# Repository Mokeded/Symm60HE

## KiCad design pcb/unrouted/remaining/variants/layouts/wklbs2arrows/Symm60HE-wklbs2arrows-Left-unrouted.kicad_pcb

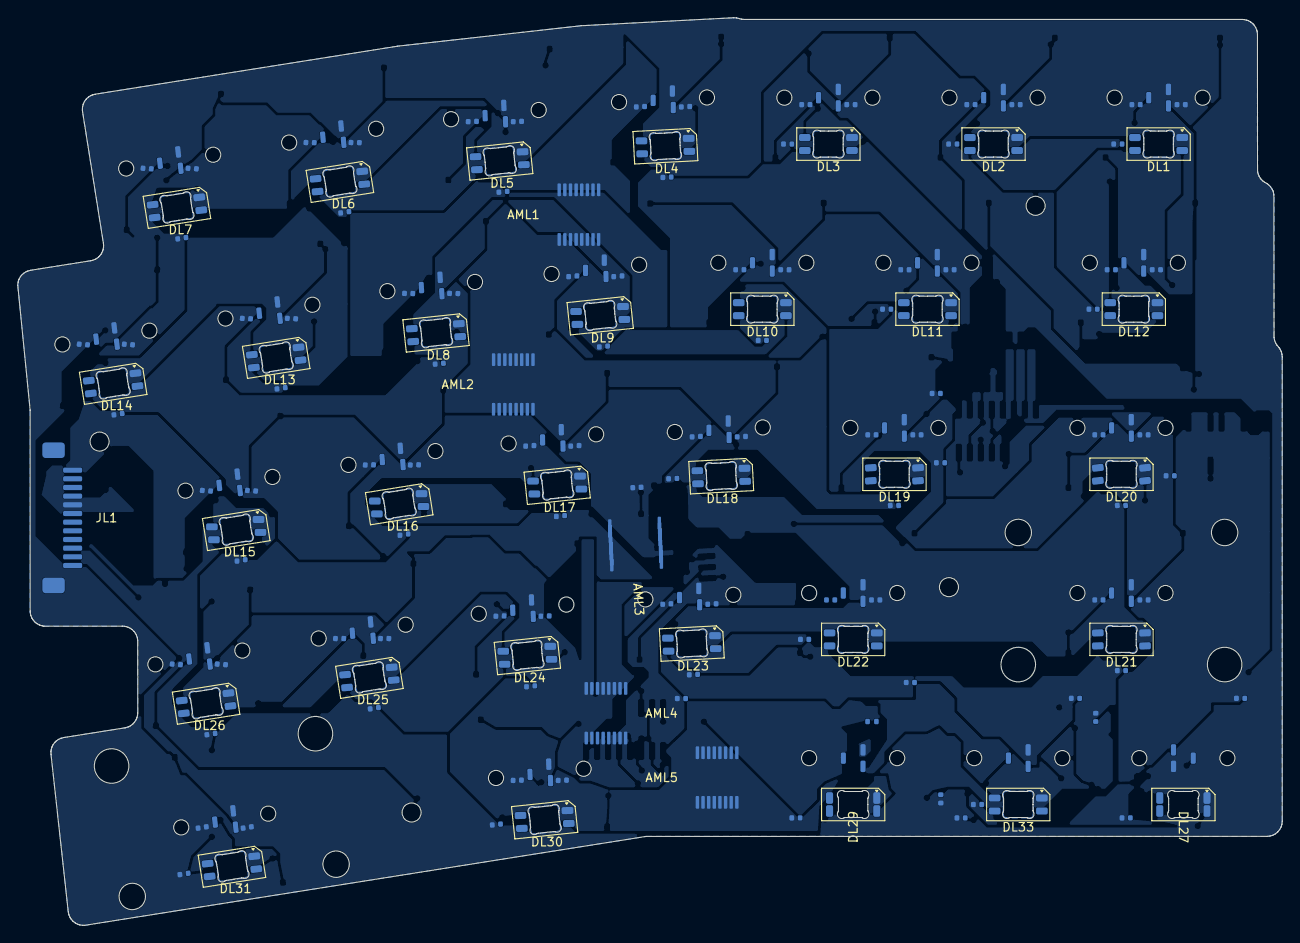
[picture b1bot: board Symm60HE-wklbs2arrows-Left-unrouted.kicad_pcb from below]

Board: 2 copper layers, 145.9 x 104.7 mm, 173 parts (167 on the bottom side), 73 nets, no tracks yet.

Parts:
AML1, AML2, AML3, AML4, AML5: SN74LV4051A; AM1_TSSOP-16_4.4x5mm_P0.65mm
CL1A, CL2A, CL3A, CL4A, CL5A, CL6A, CL7A, CL8A, CL9A, CL10A, CL11A, CL12A, CL13A, CL14A, CL15A, CL16A, CL17A, CL18A, CL19A, CL20A, CL21A, CL22A, CL23A, CL24A, CL25A, CL26A, CL27A, CL29A, CL31A, CL32A, CL33A: 100n; C1_C_0402_1005Metric
CL1B, CL2B, CL3B, CL4B, CL5B, CL6B, CL7B, CL8B, CL9B, CL10B, CL11B, CL12B, CL13B, CL14B, CL15B, CL16B, CL17B, CL18B, CL19B, CL20B, CL21B, CL22B, CL23B, CL24B, CL25B, CL26B, CL27B, CL29B, CL31B, CL32B, CL33B: 4.7n; C1_C_0402_1005Metric
CML1, CML2, CML3, CML4, CML5: 100n; C1_C_0402_1005Metric
CRGBL1, CRGBL2, CRGBL3, CRGBL4, CRGBL5, CRGBL6, CRGBL7, CRGBL8, CRGBL9, CRGBL10, CRGBL11, CRGBL12, CRGBL13, CRGBL14, CRGBL15, CRGBL16, CRGBL17, CRGBL18, CRGBL19, CRGBL20, CRGBL21, CRGBL22, CRGBL23, CRGBL24, CRGBL25, CRGBL26, CRGBL27, CRGBL29, CRGBL30, CRGBL31, CRGBL33: 100n; C1_C_0402_1005Metric
DL1, DL2, DL3, DL4, DL5, DL6, DL7, DL8, DL9, DL10, DL11, DL12, DL13, DL14, DL15, DL16, DL17, DL18, DL19, DL20, DL21, DL22, DL23, DL24, DL25, DL26, DL27, DL29, DL30, DL31, DL33: SK6812MINI-E; SK6812MINI-E_ReverseMount
HEL1, HEL2, HEL3, HEL4, HEL5, HEL6, HEL7, HEL9, HEL10, HEL11, HEL12, HEL13, HEL14, HEL16, HEL17, HEL18, HEL19, HEL20, HEL22, HEL23, HEL24, HEL25, HEL26, HEL27, HEL29, HEL31: MT9102ET; HE_KEY_1.00u
HEL8, HEL32: MT9102ET; HE_KEY_1.50u
HEL15: MT9102ET; HE_KEY_1.75u
HEL21, HEL33: MT9102ET; HE_KEY_2.25u
JL1: FFC_12P; FFC_12P_1.00mm_TopContact
MHL1, MHL2, MHL3, MHL4: M2_NPTH; MountingHole_2.2mm_M2_NPTH
RBPL29: 0R_DNP; R3_R_0402_1005Metric
SL1, SL2: STAB_MX; STABILIZER_MX_2U

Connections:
+3V3A: AML1.16, AML2.16, AML3.16, AML4.16, AML5.16, CL1A.1, CL2A.1, CL3A.1, CL4A.1, CL5A.1, CL6A.1, CL7A.1, CL8A.1, CL9A.1, CL10A.1, CL11A.1, CL12A.1, CL13A.1, CL14A.1, CL15A.1, CL16A.1, CL17A.1, CL18A.1, CL19A.1, CL20A.1, CL21A.1, CL22A.1, CL23A.1, CL24A.1, CL25A.1, CL26A.1, CL27A.1, CL29A.1, CL31A.1, CL32A.1, CL33A.1, CML1.1, CML2.1, CML3.1, CML4.1, CML5.1, HEL1.1, HEL2.1, HEL3.1, HEL4.1, HEL5.1, HEL6.1, HEL7.1, HEL8.1, HEL9.1, HEL10.1, HEL11.1, HEL12.1, HEL13.1, HEL14.1, HEL15.1, HEL16.1, HEL17.1, HEL18.1, HEL19.1, HEL20.1, HEL21.1, HEL22.1, HEL23.1, HEL24.1, HEL25.1, HEL26.1, HEL27.1, HEL29.1, HEL31.1, HEL32.1, HEL33.1, JL1.12
ADC_L1: AML1.3, JL1.6
ADC_L2: AML2.3, JL1.4
ADC_L3: AML3.3, JL1.2
ADC_L4: AML4.3, JL1.1
ADC_L5: AML5.3, JL1.11
GND: AML1.6, AML1.7, AML1.8, AML2.6, AML2.7, AML2.8, AML3.6, AML3.7, AML3.8, AML4.4, AML4.6, AML4.7, AML4.8, AML5.1, AML5.2, AML5.4, AML5.5, AML5.6, AML5.7, AML5.8, AML5.12, AML5.15, CL1A.2, CL1B.2, CL2A.2, CL2B.2, CL3A.2, CL3B.2, CL4A.2, CL4B.2, CL5A.2, CL5B.2, CL6A.2, CL6B.2, CL7A.2, CL7B.2, CL8A.2, CL8B.2, CL9A.2, CL9B.2, CL10A.2, CL10B.2, CL11A.2, CL11B.2, CL12A.2, CL12B.2, CL13A.2, CL13B.2, CL14A.2, CL14B.2, CL15A.2, CL15B.2, CL16A.2, CL16B.2, CL17A.2, CL17B.2, CL18A.2, CL18B.2, CL19A.2, CL19B.2, CL20A.2, CL20B.2, CL21A.2, CL21B.2, CL22A.2, CL22B.2, CL23A.2, CL23B.2, CL24A.2, CL24B.2, CL25A.2, CL25B.2, CL26A.2, CL26B.2, CL27A.2, CL27B.2, CL29A.2, CL29B.2, CL31A.2, CL31B.2, CL32A.2, CL32B.2, CL33A.2, CL33B.2, CML1.2, CML2.2, CML3.2, CML4.2, CML5.2, CRGBL1.2, CRGBL2.2, CRGBL3.2, CRGBL4.2, CRGBL5.2, CRGBL6.2, CRGBL7.2, CRGBL8.2, CRGBL9.2, CRGBL10.2, CRGBL11.2, CRGBL12.2, CRGBL13.2, CRGBL14.2, CRGBL15.2, CRGBL16.2, CRGBL17.2, CRGBL18.2, CRGBL19.2, CRGBL20.2, CRGBL21.2, CRGBL22.2, CRGBL23.2, CRGBL24.2, CRGBL25.2, CRGBL26.2, CRGBL27.2, CRGBL29.2, CRGBL30.2, CRGBL31.2, CRGBL33.2, DL1.1, DL2.1, DL3.1, DL4.1, DL5.1, DL6.1, DL7.1, DL8.1, DL9.1, DL10.1, DL11.1, DL12.1, DL13.1, DL14.1, DL15.1, DL16.1, DL17.1, DL18.1, DL19.1, DL20.1, DL21.1, DL22.1, DL23.1, DL24.1, DL25.1, DL26.1, DL27.1, DL29.1, DL30.1, DL31.1, DL33.1, HEL1.2, HEL2.2, HEL3.2, HEL4.2, HEL5.2, HEL6.2, HEL7.2, HEL8.2, HEL9.2, HEL10.2, HEL11.2, HEL12.2, HEL13.2, HEL14.2, HEL15.2, HEL16.2, HEL17.2, HEL18.2, HEL19.2, HEL20.2, HEL21.2, HEL22.2, HEL23.2, HEL24.2, HEL25.2, HEL26.2, HEL27.2, HEL29.2, HEL31.2, HEL32.2, HEL33.2, JL1.5
HE_L01: AML1.13, CL1B.1, HEL1.3
HE_L02: AML1.14, CL2B.1, HEL2.3
HE_L03: AML1.15, CL3B.1, HEL3.3
HE_L04: AML1.12, CL4B.1, HEL4.3
HE_L05: AML1.1, CL5B.1, HEL5.3
HE_L06: AML1.5, CL6B.1, HEL6.3
HE_L07: AML1.2, CL7B.1, HEL7.3
HE_L08: AML1.4, CL8B.1, HEL8.3
HE_L09: AML2.13, CL9B.1, HEL9.3
HE_L10: AML2.14, CL10B.1, HEL10.3
HE_L11: AML2.15, CL11B.1, HEL11.3
HE_L12: AML2.12, CL12B.1, HEL12.3
HE_L13: AML2.1, CL13B.1, HEL13.3
HE_L14: AML2.5, CL14B.1, HEL14.3
HE_L15: AML2.2, CL15B.1, HEL15.3
HE_L16: AML2.4, CL16B.1, HEL16.3
HE_L17: AML3.13, CL17B.1, HEL17.3
HE_L18: AML3.14, CL18B.1, HEL18.3
HE_L19: AML3.15, CL19B.1, HEL19.3
HE_L20: AML3.12, CL20B.1, HEL20.3
HE_L21: AML3.1, CL21B.1, HEL21.3
HE_L22: AML3.5, CL22B.1, HEL22.3
HE_L23: AML3.2, CL23B.1, HEL23.3
HE_L24: AML3.4, CL24B.1, HEL24.3
HE_L25: AML4.13, CL25B.1, HEL25.3
HE_L26: AML4.14, CL26B.1, HEL26.3
HE_L27: AML4.15, CL27B.1, HEL27.3
HE_L28: AML4.12, CL29B.1, HEL29.3
HE_L29: AML4.1, CL31B.1, HEL31.3
HE_L30: AML4.5, CL32B.1, HEL32.3
HE_L31: AML4.2, CL33B.1, HEL33.3
MUX_A0: AML1.11, AML2.11, AML3.11, AML4.11, AML5.11, JL1.10
MUX_A1: AML1.10, AML2.10, AML3.10, AML4.10, AML5.10, JL1.9
MUX_A2: AML1.9, AML2.9, AML3.9, AML4.9, AML5.9, JL1.8
RGB_L: DL1.2, JL1.3
RGB_L_01: DL1.4, DL2.2
RGB_L_02: DL2.4, DL3.2
RGB_L_03: DL3.4, DL4.2
RGB_L_04: DL4.4, DL5.2
RGB_L_05: DL5.4, DL6.2
RGB_L_06: DL6.4, DL7.2
RGB_L_07: DL7.4, DL8.2
RGB_L_08: DL8.4, DL9.2
RGB_L_09: DL9.4, DL10.2
RGB_L_10: DL10.4, DL11.2
RGB_L_11: DL11.4, DL12.2
RGB_L_12: DL12.4, DL13.2
RGB_L_13: DL13.4, DL14.2
RGB_L_14: DL14.4, DL15.2
RGB_L_15: DL15.4, DL16.2
RGB_L_16: DL16.4, DL17.2
RGB_L_17: DL17.4, DL18.2
RGB_L_18: DL18.4, DL19.2
RGB_L_19: DL19.4, DL20.2
RGB_L_20: DL20.4, DL21.2
RGB_L_21: DL21.4, DL22.2
RGB_L_22: DL22.4, DL23.2
RGB_L_23: DL23.4, DL24.2
RGB_L_24: DL24.4, DL25.2
RGB_L_25: DL25.4, DL26.2
RGB_L_26: DL26.4, DL27.2
RGB_L_27: DL27.4, DL33.2
RGB_L_28: DL29.2, DL33.4, RBPL29.1
RGB_L_29: DL29.4, DL30.2, RBPL29.2
RGB_L_30: DL30.4, DL31.2
VBUS: CRGBL1.1, CRGBL2.1, CRGBL3.1, CRGBL4.1, CRGBL5.1, CRGBL6.1, CRGBL7.1, CRGBL8.1, CRGBL9.1, CRGBL10.1, CRGBL11.1, CRGBL12.1, CRGBL13.1, CRGBL14.1, CRGBL15.1, CRGBL16.1, CRGBL17.1, CRGBL18.1, CRGBL19.1, CRGBL20.1, CRGBL21.1, CRGBL22.1, CRGBL23.1, CRGBL24.1, CRGBL25.1, CRGBL26.1, CRGBL27.1, CRGBL29.1, CRGBL30.1, CRGBL31.1, CRGBL33.1, DL1.3, DL2.3, DL3.3, DL4.3, DL5.3, DL6.3, DL7.3, DL8.3, DL9.3, DL10.3, DL11.3, DL12.3, DL13.3, DL14.3, DL15.3, DL16.3, DL17.3, DL18.3, DL19.3, DL20.3, DL21.3, DL22.3, DL23.3, DL24.3, DL25.3, DL26.3, DL27.3, DL29.3, DL30.3, DL31.3, DL33.3, JL1.7

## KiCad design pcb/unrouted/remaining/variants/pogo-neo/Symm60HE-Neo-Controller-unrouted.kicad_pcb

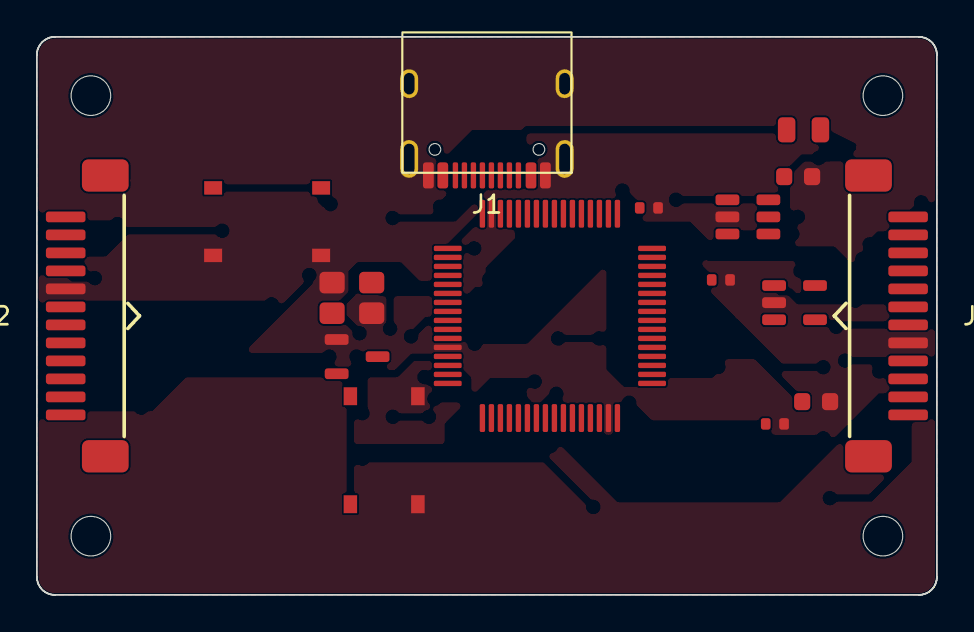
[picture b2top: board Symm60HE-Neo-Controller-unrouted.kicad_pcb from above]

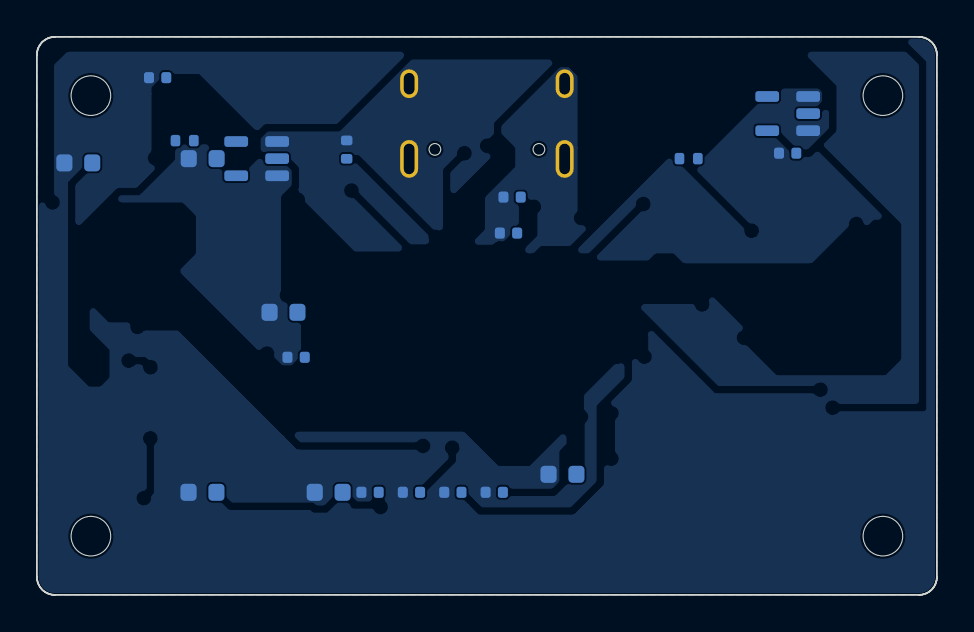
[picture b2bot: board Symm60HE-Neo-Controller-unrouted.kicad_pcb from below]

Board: 2 copper layers, 50.0 x 31.0 mm, 40 parts (20 on the bottom side), 33 nets, no tracks yet.

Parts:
C1, C8: 10u; C148_C_0603_1608Metric
C2, C10: 1u; C148_C_0603_1608Metric
C3, C4: 30p; C1_C_0402_1005Metric
C5, C6, C7, C9, C11, C16, C17: 100n; C1_C_0402_1005Metric
C12, C13, C14, C15: 2.2u; C148_C_0603_1608Metric
F1: 0.5A; F1_Fuse_0805_2012Metric
J1: TYPE-C-31-M-12; USB_C_Receptacle_HRO_TYPE-C-31-M-12
J2, J3: FFC_12P; FFC_12P_1.00mm_TopContact
MHD1, MHD2, MHD3, MHD4: M2_NPTH; MountingHole_2.2mm_M2_NPTH
R1, R4: 12k; R3_R_0402_1005Metric
R2, R3: 5.1k; R3_R_0402_1005Metric
R5, R6: 470R; R3_R_0402_1005Metric
SW1, SW2: TS-1187A; SW1_SW_Push_1P1T_XKB_TS-1187A
U1: AT32F405RCT7; U4_LQFP-64_10x10mm_P0.5mm
U2: USBLC6-2SC6; U1_SOT-23-6
U3: TLV75733PDBV; U2_SOT-23-5
U4: XC6206P332MR; U3_SOT-23-3
U5, U6: SN74AHCT1G125; U2_SOT-23-5
Y1: 12MHz; Y1_Crystal_SMD_3225-4Pin_3.2x2.5mm

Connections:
+3V3A: C9.1, C10.1, C15.1, J2.1, J3.1, U1.13, U4.2
+3V3D: C2.1, C5.1, C6.1, C7.1, C8.1, C13.1, C14.1, U1.1, U1.36, U1.64, U3.5, U4.3
ADC_L1: J2.7, U1.17
ADC_L2: J2.9, U1.20
ADC_L3: J2.11, U1.21
ADC_L4: J2.12, U1.22
ADC_L5: J2.2, U1.16
ADC_R1: J3.7, U1.23
ADC_R2: J3.9, U1.24
ADC_R3: J3.11, U1.25
ADC_R4: J3.12, U1.26
ADC_R5: J3.2, U1.15
BOOT0: R4.1, SW1.1, U1.60
CC1: J1.A5, R2.1
CC2: J1.B5, R3.1
GND: C1.2, C2.2, C3.2, C4.2, C5.2, C6.2, C7.2, C8.2, C9.2, C10.2, C11.2, C12.2, C13.2, C14.2, C15.2, C16.2, C17.2, J1.A1, J1.A12, J1.B1, J1.B12, J1.SH, J2.8, J3.8, R1.2, R2.2, R3.2, R4.2, SW1.2, SW2.2, U1.12, U1.31, U1.63, U2.2, U3.2, U4.1, U5.1, U5.3, U6.1, U6.3, Y1.2, Y1.4
MUX_A0: J2.3, J3.3, U1.9
MUX_A1: J2.4, J3.4, U1.10
MUX_A2: J2.5, J3.5, U1.11
NRST: C11.1, SW2.1, U1.7
RGB_L: J2.10, R5.2
RGB_L_BUF: R5.1, U5.4
RGB_L_MCU: U1.8, U5.2
RGB_R: J3.10, R6.2
RGB_R_BUF: R6.1, U6.4
RGB_R_MCU: U1.41, U6.2
USB_DM: J1.A7, J1.B7, U1.34, U2.3, U2.4
USB_DP: J1.A6, J1.B6, U1.35, U2.1, U2.6
USB_R: R1.1, U1.33
VBUS: C1.1, C12.1, C16.1, C17.1, F1.2, J2.6, J3.6, U2.5, U3.1, U5.5, U6.5
VBUS_IN: F1.1, J1.A4, J1.A9, J1.B4, J1.B9
XTAL_IN: C3.1, U1.5, Y1.1
XTAL_OUT: C4.1, U1.6, Y1.3

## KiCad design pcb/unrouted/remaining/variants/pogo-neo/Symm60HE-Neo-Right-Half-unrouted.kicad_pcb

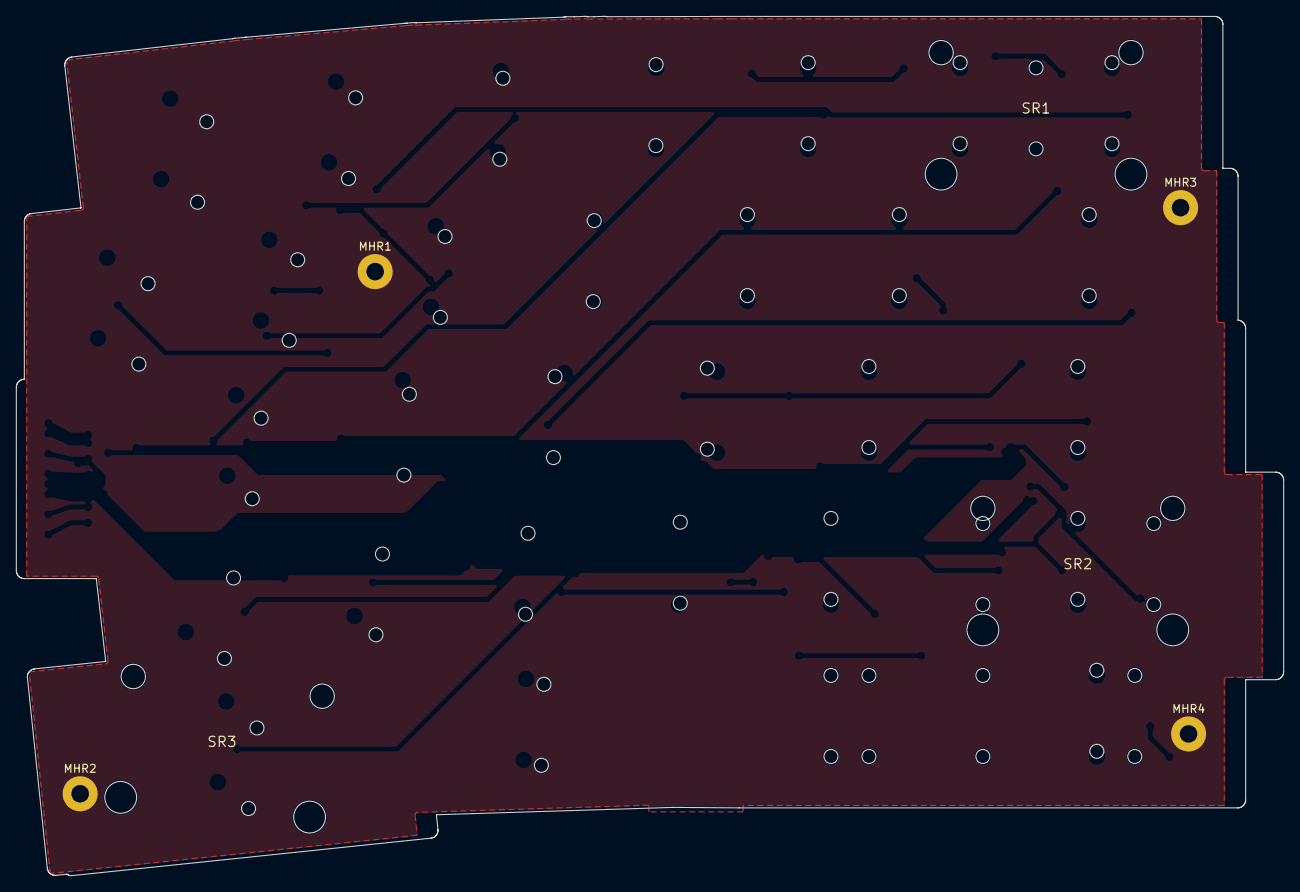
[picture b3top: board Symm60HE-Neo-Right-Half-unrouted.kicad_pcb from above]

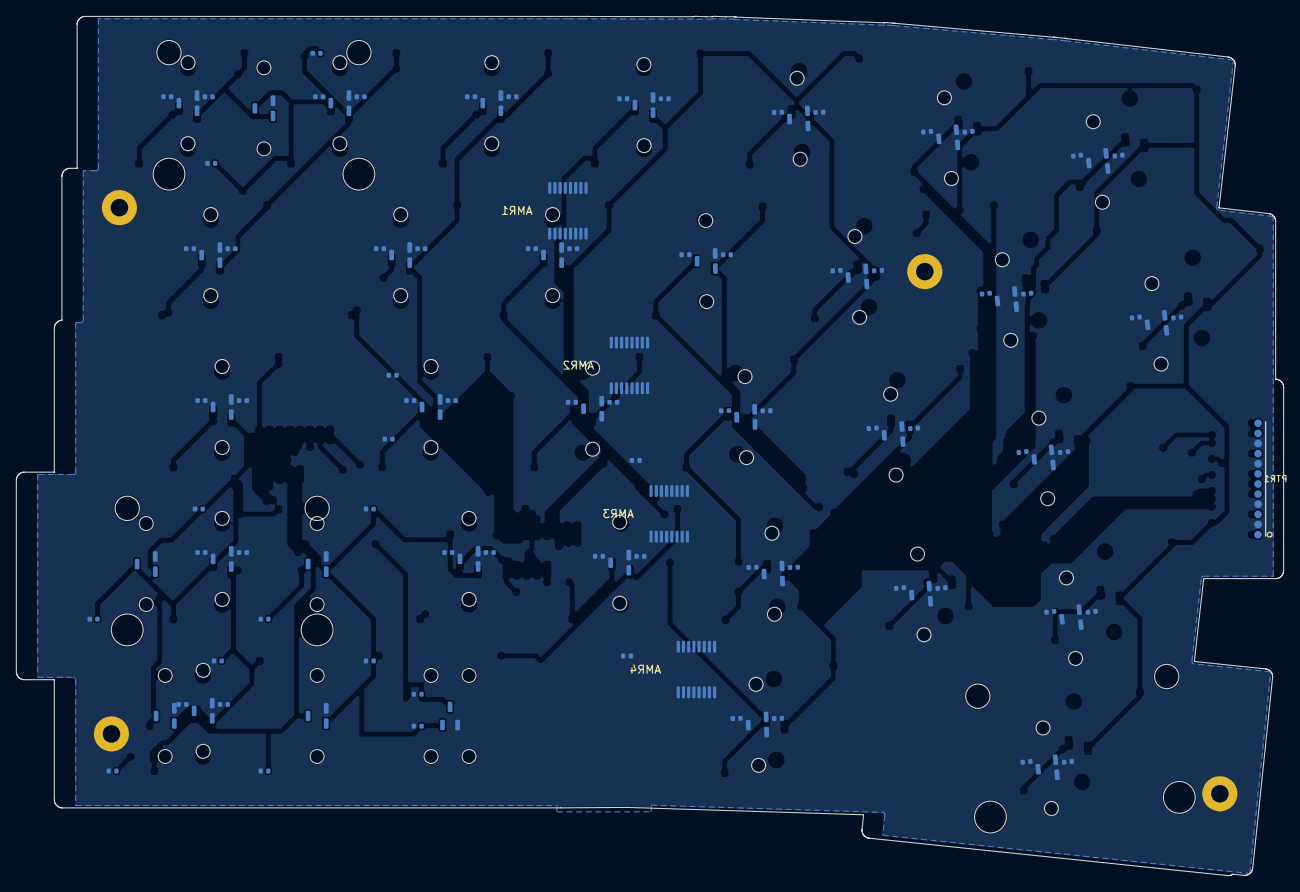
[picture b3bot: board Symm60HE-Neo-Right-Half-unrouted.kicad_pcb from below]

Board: 2 copper layers, 158.9 x 107.8 mm, 123 parts (116 on the bottom side), 41 nets, no tracks yet.

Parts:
AMR1, AMR2, AMR3, AMR4: SN74LV4051A; AM1_TSSOP-16_4.4x5mm_P0.65mm
CMR1, CMR2, CMR3, CMR4: 100n; C1_C_0402_1005Metric
CR1A, CR2A, CR3A, CR4A, CR5A, CR6A, CR7A, CR8A, CR9A, CR10A, CR11A, CR12A, CR13A, CR14A, CR15A, CR16A, CR17A, CR18A, CR19A, CR20A, CR21A, CR22A, CR23A, CR24A, CR25A, CR26A, CR27A, CR28A, CR29A, CR30A, CR32A, CR33A, CR34A, CR35A, CR36A: 100n; C1_C_0402_1005Metric
CR1B, CR2B, CR3B, CR4B, CR5B, CR6B, CR7B, CR8B, CR9B, CR10B, CR11B, CR12B, CR13B, CR14B, CR15B, CR16B, CR17B, CR18B, CR19B, CR20B, CR21B, CR22B, CR23B, CR24B, CR25B, CR26B, CR27B, CR28B, CR29B, CR30B, CR32B, CR33B, CR34B, CR35B, CR36B: 4.7n; C1_C_0402_1005Metric
HER1, HER2, HER3, HER5, HER6, HER7, HER8, HER9, HER10, HER12, HER13, HER14, HER15, HER16, HER17, HER19, HER20, HER21, HER22, HER23, HER24, HER27, HER28, HER29, HER32, HER34: MT9102ET; HE_KEY_1.00u
HER4: MT9102ET; HE_KEY_2.00u
HER11, HER33, HER35: MT9102ET; HE_KEY_1.50u
HER18: MT9102ET; HE_KEY_1.75u
HER25, HER36: MT9102ET; HE_KEY_2.25u
HER26: MT9102ET; HE_KEY_1.25u
HER30: MT9102ET; HE_SHARED_MIDPOINT
KMR30A, KMR30N: MX_MECHANICAL_ONLY; HE_KEY_MECHANICAL_ONLY
MHR1, MHR2, MHR3, MHR4: M2; MountingHole_2.2mm_M2_Pad
PTR1: 856-10-012-30-051000; MillMax_856-10-012-30-051000
SR1, SR2, SR3: STAB_MX; STABILIZER_MX_2U

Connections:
+3V3A: AMR1.16, AMR2.16, AMR3.16, AMR4.16, CMR1.1, CMR2.1, CMR3.1, CMR4.1, CR1A.1, CR2A.1, CR3A.1, CR4A.1, CR5A.1, CR6A.1, CR7A.1, CR8A.1, CR9A.1, CR10A.1, CR11A.1, CR12A.1, CR13A.1, CR14A.1, CR15A.1, CR16A.1, CR17A.1, CR18A.1, CR19A.1, CR20A.1, CR21A.1, CR22A.1, CR23A.1, CR24A.1, CR25A.1, CR26A.1, CR27A.1, CR28A.1, CR29A.1, CR30A.1, CR32A.1, CR33A.1, CR34A.1, CR35A.1, CR36A.1, HER1.1, HER2.1, HER3.1, HER4.1, HER5.1, HER6.1, HER7.1, HER8.1, HER9.1, HER10.1, HER11.1, HER12.1, HER13.1, HER14.1, HER15.1, HER16.1, HER17.1, HER18.1, HER19.1, HER20.1, HER21.1, HER22.1, HER23.1, HER24.1, HER25.1, HER26.1, HER27.1, HER28.1, HER29.1, HER30.1, HER32.1, HER33.1, HER34.1, HER35.1, HER36.1, PTR1.1
ADC_R1: AMR1.3, PTR1.7
ADC_R2: AMR2.3, PTR1.9
ADC_R3: AMR3.3, PTR1.11
ADC_R4: AMR4.3, PTR1.12
GND: AMR1.6, AMR1.7, AMR1.8, AMR2.6, AMR2.7, AMR2.8, AMR3.6, AMR3.7, AMR3.8, AMR4.6, AMR4.7, AMR4.8, CMR1.2, CMR2.2, CMR3.2, CMR4.2, CR1A.2, CR1B.2, CR2A.2, CR2B.2, CR3A.2, CR3B.2, CR4A.2, CR4B.2, CR5A.2, CR5B.2, CR6A.2, CR6B.2, CR7A.2, CR7B.2, CR8A.2, CR8B.2, CR9A.2, CR9B.2, CR10A.2, CR10B.2, CR11A.2, CR11B.2, CR12A.2, CR12B.2, CR13A.2, CR13B.2, CR14A.2, CR14B.2, CR15A.2, CR15B.2, CR16A.2, CR16B.2, CR17A.2, CR17B.2, CR18A.2, CR18B.2, CR19A.2, CR19B.2, CR20A.2, CR20B.2, CR21A.2, CR21B.2, CR22A.2, CR22B.2, CR23A.2, CR23B.2, CR24A.2, CR24B.2, CR25A.2, CR25B.2, CR26A.2, CR26B.2, CR27A.2, CR27B.2, CR28A.2, CR28B.2, CR29A.2, CR29B.2, CR30A.2, CR30B.2, CR32A.2, CR32B.2, CR33A.2, CR33B.2, CR34A.2, CR34B.2, CR35A.2, CR35B.2, CR36A.2, CR36B.2, HER1.2, HER2.2, HER3.2, HER4.2, HER5.2, HER6.2, HER7.2, HER8.2, HER9.2, HER10.2, HER11.2, HER12.2, HER13.2, HER14.2, HER15.2, HER16.2, HER17.2, HER18.2, HER19.2, HER20.2, HER21.2, HER22.2, HER23.2, HER24.2, HER25.2, HER26.2, HER27.2, HER28.2, HER29.2, HER30.2, HER32.2, HER33.2, HER34.2, HER35.2, HER36.2, MHR1.1, MHR2.1, MHR3.1, MHR4.1, PTR1.2, PTR1.4, PTR1.8, PTR1.10
HE_R01: AMR1.13, CR6B.1, HER6.3
HE_R02: AMR1.14, CR1B.1, HER1.3
HE_R03: AMR1.15, CR2B.1, HER2.3
HE_R04: AMR1.12, CR3B.1, CR4B.1, HER3.3, HER4.3
HE_R05: AMR1.1, CR5B.1, HER5.3
HE_R06: AMR1.5, CR7B.1, HER7.3
HE_R07: AMR1.2, CR8B.1, HER8.3
HE_R08: AMR1.4, CR13B.1, HER13.3
HE_R09: AMR2.13, CR12B.1, HER12.3
HE_R10: AMR2.14, CR9B.1, HER9.3
HE_R11: AMR2.15, CR10B.1, HER10.3
HE_R12: AMR2.12, CR11B.1, HER11.3
HE_R13: AMR2.1, CR14B.1, HER14.3
HE_R14: AMR2.5, CR15B.1, HER15.3
HE_R15: AMR2.2, CR19B.1, HER19.3
HE_R16: AMR2.4, CR16B.1, HER16.3
HE_R17: AMR3.13, CR17B.1, HER17.3
HE_R18: AMR3.14, CR18B.1, HER18.3
HE_R19: AMR3.15, CR20B.1, HER20.3
HE_R20: AMR3.12, CR21B.1, HER21.3
HE_R21: AMR3.1, CR27B.1, HER27.3
HE_R22: AMR3.5, CR22B.1, HER22.3
HE_R23: AMR3.2, CR23B.1, HER23.3
HE_R24: AMR3.4, CR24B.1, HER24.3
HE_R25: AMR4.13, CR25B.1, CR26B.1, HER25.3, HER26.3
HE_R26: AMR4.14, CR28B.1, HER28.3
HE_R27: AMR4.15, CR29B.1, HER29.3
HE_R28: AMR4.12, CR35B.1, HER35.3
HE_R29: AMR4.1, CR30B.1, HER30.3
HE_R30: AMR4.5, CR32B.1, CR33B.1, HER32.3, HER33.3
HE_R31: AMR4.2, CR34B.1, HER34.3
HE_R32: AMR4.4, CR36B.1, HER36.3
MUX_A0: AMR1.11, AMR2.11, AMR3.11, AMR4.11, PTR1.3
MUX_A1: AMR1.10, AMR2.10, AMR3.10, AMR4.10, PTR1.5
MUX_A2: AMR1.9, AMR2.9, AMR3.9, AMR4.9, PTR1.6

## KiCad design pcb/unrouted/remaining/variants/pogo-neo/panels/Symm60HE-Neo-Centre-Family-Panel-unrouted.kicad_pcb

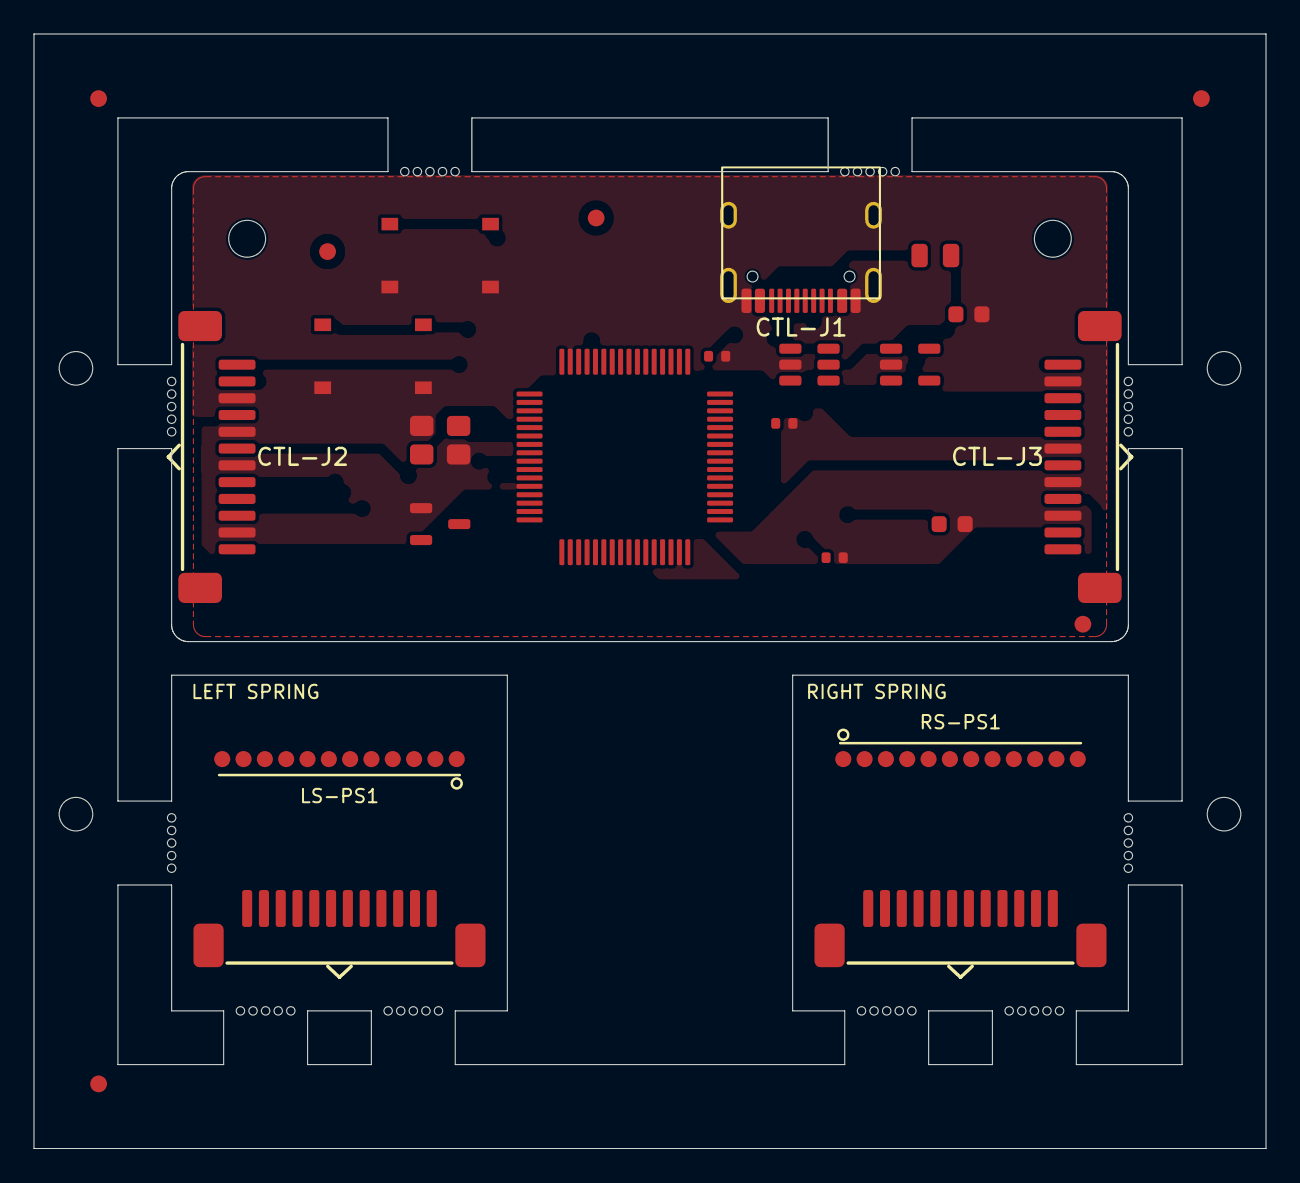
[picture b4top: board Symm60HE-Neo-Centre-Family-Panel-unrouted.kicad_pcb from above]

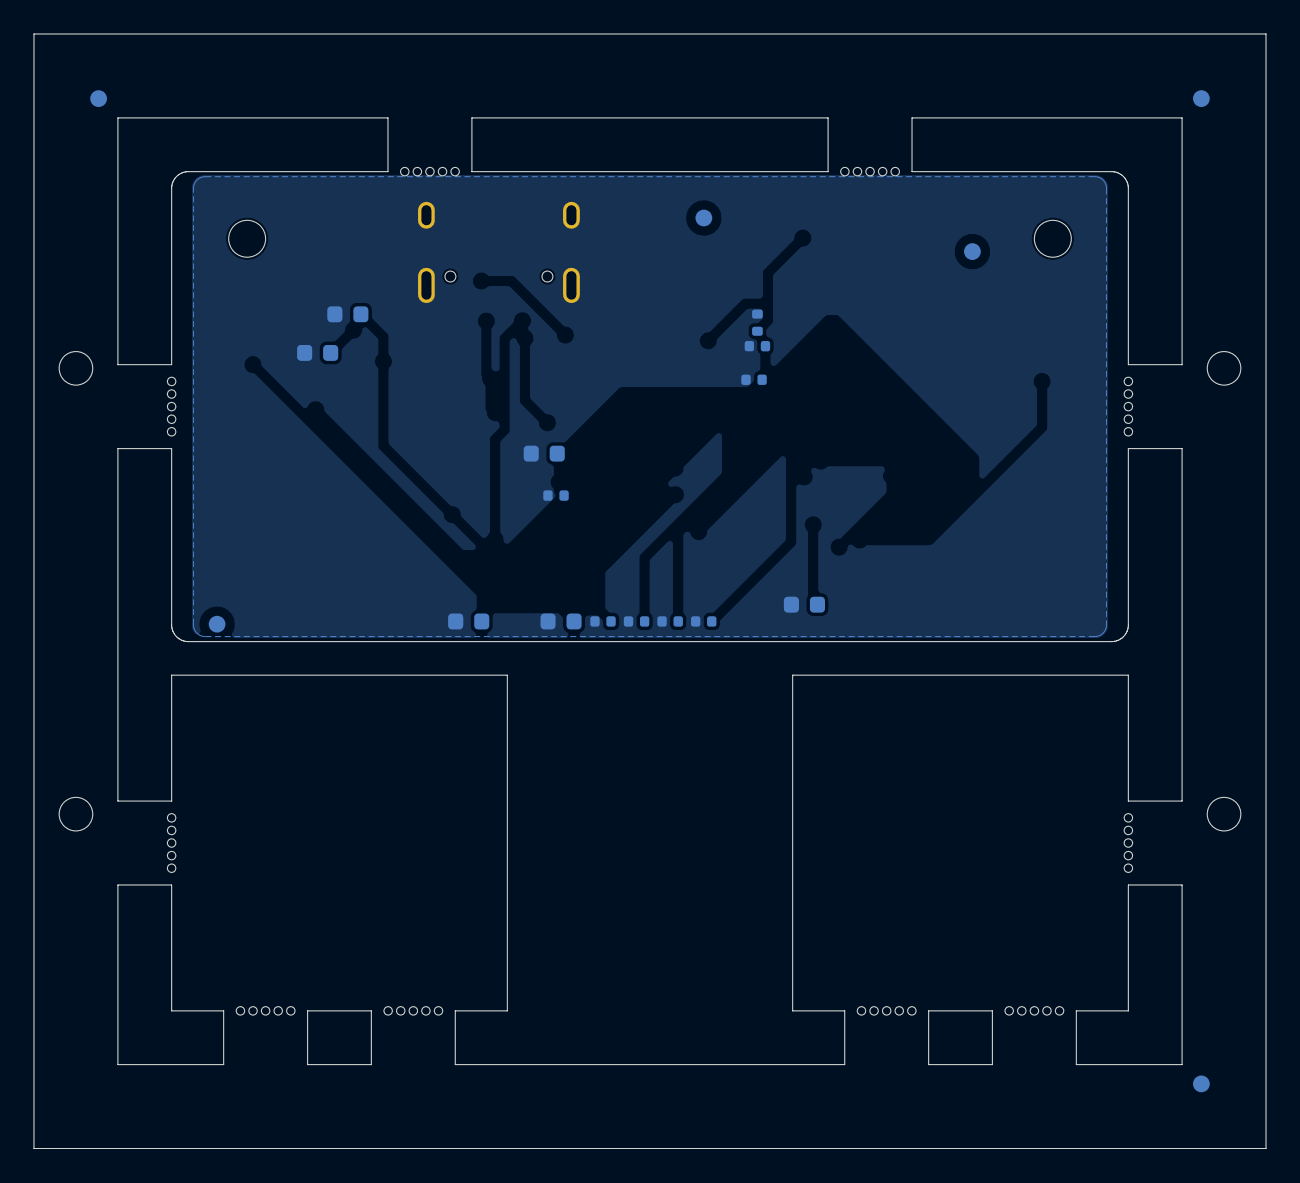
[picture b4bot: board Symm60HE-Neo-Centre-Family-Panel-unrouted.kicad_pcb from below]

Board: 2 copper layers, 73.4 x 66.4 mm, 102 parts (20 on the bottom side), 43 nets, no tracks yet.

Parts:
CTL-C1, CTL-C8: 10u; C148_C_0603_1608Metric
CTL-C2, CTL-C10: 1u; C148_C_0603_1608Metric
CTL-C3, CTL-C4: 30p; C1_C_0402_1005Metric
CTL-C5, CTL-C6, CTL-C7, CTL-C9, CTL-C11: 100n; C1_C_0402_1005Metric
CTL-C12, CTL-C13, CTL-C14, CTL-C15: 2.2u; C148_C_0603_1608Metric
CTL-F1: 0.5A; F1_Fuse_0805_2012Metric
CTL-FIDB1, CTL-FIDB2, CTL-FIDB3: FIDUCIAL_1MM_BCU; Fiducial_1mm_BCu
CTL-FIDF1, CTL-FIDF2, CTL-FIDF3: FIDUCIAL_1MM_FCU; Fiducial_1mm_FCu
CTL-J1: TYPE-C-31-M-12; USB_C_Receptacle_HRO_TYPE-C-31-M-12
CTL-J2, CTL-J3: FFC_12P; FFC_12P_1.00mm_TopContact
CTL-MHD1, CTL-MHD2: M2_NPTH; MountingHole_2.2mm_M2_NPTH
CTL-R1, CTL-R4: 12k; R3_R_0402_1005Metric
CTL-R2, CTL-R3: 5.1k; R3_R_0402_1005Metric
CTL-SW1, CTL-SW2: TS-1187A; SW1_SW_Push_1P1T_XKB_TS-1187A
CTL-U1: AT32F405RCT7; U4_LQFP-64_10x10mm_P0.5mm
CTL-U2: USBLC6-2SC6; U1_SOT-23-6
CTL-U3: TLV75733PDBV; U2_SOT-23-5
CTL-U4: XC6206P332MR; U3_SOT-23-3
CTL-Y1: 12MHz; Y1_Crystal_SMD_3225-4Pin_3.2x2.5mm
FIDB1, FIDB2, FIDB3: FIDUCIAL_1MM_BCU; Fiducial_1mm_BCu
FIDF1, FIDF2, FIDF3: FIDUCIAL_1MM_FCU; Fiducial_1mm_FCu
LS-JF1: FFC_12P_1.00mm; FFC_12P_1.00mm_TopContact
LS-PS1: 854-22-012-30-004101; MillMax_854-22-012-30-004101
MB1, MB2, MB3, MB4, MB5, MB6, MB7, MB8, MB9, MB10, MB11, MB12, MB13, MB14, MB15, MB16, MB17, MB18, MB19, MB20, MB21, MB22, MB23, MB24, MB25, MB26, MB27, MB28, MB29, MB30, MB31, MB32, MB33, MB34, MB35, MB36, MB37, MB38, MB39, MB40, MB41, MB42, MB43, MB44, MB45, MB46, MB47, MB48, MB49, MB50: MOUSE_BITE_0.5MM; MouseBite_0.5mm
RS-JF1: FFC_12P_1.00mm; FFC_12P_1.00mm_TopContact
RS-PS1: 854-22-012-30-004101; MillMax_854-22-012-30-004101
TH1, TH2, TH3, TH4: TOOLING_HOLE_2MM; ToolingHole_2mm_NPTH

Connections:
/CTL/+3V3A: CTL-C9.1, CTL-C10.1, CTL-C15.1, CTL-J2.12, CTL-J3.12, CTL-U1.13, CTL-U4.2
/CTL/+3V3D: CTL-C2.1, CTL-C5.1, CTL-C6.1, CTL-C7.1, CTL-C8.1, CTL-C13.1, CTL-C14.1, CTL-U1.1, CTL-U1.36, CTL-U1.64, CTL-U3.5, CTL-U4.3
/CTL/ADC_L1: CTL-J2.6, CTL-U1.17
/CTL/ADC_L2: CTL-J2.4, CTL-U1.20
/CTL/ADC_L3: CTL-J2.2, CTL-U1.21
/CTL/ADC_L4: CTL-J2.1, CTL-U1.22
/CTL/ADC_R1: CTL-J3.6, CTL-U1.23
/CTL/ADC_R2: CTL-J3.4, CTL-U1.24
/CTL/ADC_R3: CTL-J3.2, CTL-U1.25
/CTL/ADC_R4: CTL-J3.1, CTL-U1.26
/CTL/BOOT0: CTL-R4.1, CTL-SW1.1, CTL-U1.60
/CTL/CC1: CTL-J1.A5, CTL-R2.1
/CTL/CC2: CTL-J1.B5, CTL-R3.1
/CTL/GND: CTL-C1.2, CTL-C2.2, CTL-C3.2, CTL-C4.2, CTL-C5.2, CTL-C6.2, CTL-C7.2, CTL-C8.2, CTL-C9.2, CTL-C10.2, CTL-C11.2, CTL-C12.2, CTL-C13.2, CTL-C14.2, CTL-C15.2, CTL-J1.A1, CTL-J1.A12, CTL-J1.B1, CTL-J1.B12, CTL-J1.SH, CTL-J2.3, CTL-J2.5, CTL-J2.7, CTL-J2.11, CTL-J3.3, CTL-J3.5, CTL-J3.7, CTL-J3.11, CTL-R1.2, CTL-R2.2, CTL-R3.2, CTL-R4.2, CTL-SW1.2, CTL-SW2.2, CTL-U1.12, CTL-U1.31, CTL-U1.63, CTL-U2.2, CTL-U3.2, CTL-U4.1, CTL-Y1.2, CTL-Y1.4
/CTL/MUX_A0: CTL-J2.10, CTL-J3.10, CTL-U1.9
/CTL/MUX_A1: CTL-J2.9, CTL-J3.9, CTL-U1.10
/CTL/MUX_A2: CTL-J2.8, CTL-J3.8, CTL-U1.11
/CTL/NRST: CTL-C11.1, CTL-SW2.1, CTL-U1.7
/CTL/USB_DM: CTL-J1.A7, CTL-J1.B7, CTL-U1.34, CTL-U2.3, CTL-U2.4
/CTL/USB_DP: CTL-J1.A6, CTL-J1.B6, CTL-U1.35, CTL-U2.1, CTL-U2.6
/CTL/USB_R: CTL-R1.1, CTL-U1.33
/CTL/VBUS: CTL-C1.1, CTL-C12.1, CTL-F1.2, CTL-U2.5, CTL-U3.1
/CTL/VBUS_IN: CTL-F1.1, CTL-J1.A4, CTL-J1.A9, CTL-J1.B4, CTL-J1.B9
/CTL/XTAL_IN: CTL-C3.1, CTL-U1.5, CTL-Y1.1
/CTL/XTAL_OUT: CTL-C4.1, CTL-U1.6, CTL-Y1.3
/LS/+3V3A: LS-JF1.1, LS-PS1.12
/LS/ADC_L1: LS-JF1.7, LS-PS1.6
/LS/ADC_L2: LS-JF1.9, LS-PS1.4
/LS/ADC_L3: LS-JF1.11, LS-PS1.2
/LS/ADC_L4: LS-JF1.12, LS-PS1.1
/LS/GND: LS-JF1.2, LS-JF1.6, LS-JF1.8, LS-JF1.10, LS-PS1.3, LS-PS1.5, LS-PS1.7, LS-PS1.11
/LS/MUX_A0: LS-JF1.3, LS-PS1.10
/LS/MUX_A1: LS-JF1.4, LS-PS1.9
/LS/MUX_A2: LS-JF1.5, LS-PS1.8
/RS/+3V3A: RS-JF1.1, RS-PS1.1
/RS/ADC_R1: RS-JF1.7, RS-PS1.7
/RS/ADC_R2: RS-JF1.9, RS-PS1.9
/RS/ADC_R3: RS-JF1.11, RS-PS1.11
/RS/ADC_R4: RS-JF1.12, RS-PS1.12
/RS/GND: RS-JF1.2, RS-JF1.6, RS-JF1.8, RS-JF1.10, RS-PS1.2, RS-PS1.4, RS-PS1.8, RS-PS1.10
/RS/MUX_A0: RS-JF1.3, RS-PS1.3
/RS/MUX_A1: RS-JF1.4, RS-PS1.5
/RS/MUX_A2: RS-JF1.5, RS-PS1.6
